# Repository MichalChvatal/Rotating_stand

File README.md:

# Rotating stand controlled by ATtiny Microcontroller (Attiny13)

This repository contains firmware for controlling a 28byj-48 stepper motor using an ATtiny microcontroller. The project is designed to be power-efficient by utilizing the microcontroller's low-power sleep modes and disabling unused peripherals.

The code is written in C and is intended to be compiled with a toolchain for AVR microcontrollers, such as `avr-gcc`.

## Features

* **Selectable Drive Modes:** Choose between three different control modes at compile time:
    * **Single-Phase (Wave Drive):** Optimized for low power consumption (~148 mA).
    * **Dual-Phase (Full Drive):** Provides higher torque at the cost of increased power consumption (~260 mA).
    * **Half-Step:** Offers smoother motion but has higher power consumption (~200 mA).
* **Low Power Consumption:** The firmware is optimized for low power, with the ATtiny microcontroller consuming only 2.3 mA.
* **Timer-Based Control:** The motor is driven by a Timer/Counter0 interrupt, ensuring precise and reliable stepping.
* **Sleep Mode:** The microcontroller enters an Idle sleep mode between steps to further reduce power consumption.

## Hardware Requirements

* **Microcontroller:** ATtiny (The code is based on an ATtiny, but should be adaptable to other AVR microcontrollers).
* **Stepper Motor:** 28byj-48 (5V)
* **Motor Driver:** ULN2003
* **Clock Source:** The microcontroller is configured to use an internal clock of 4.8 MHz.

### PCB Design Files

The repository includes the PCB design files in the `HW` folder. These files can be used to manufacture the custom circuit board for this project.

***

## Configuration

### Fuses

The ATtiny microcontroller's fuses must be configured as follows to achieve the desired clock speed and low power operation:

* **Low Fuse Byte:** `0x79`
* **High Fuse Byte Byte:** `0xFF`

These settings will:
* Set the internal clock to 4.8 MHz.
* Disable the internal clock division by 8.
* Disable the Brown-out Detection (BODLEVEL).
* Disable the Watchdog Timer.

### Drive Mode Selection

You can select the desired drive mode by modifying the `#define` statements at the top of the `main.c` file. Only one mode should be set to `1` at a time.

```c
// Select control type
#define SINGLE_PHASE_CONTROL (1) // Wave drive - Full step; single-phase control. (Consumption 148 mA)
#define DUAL_PHASE_CONTROL   (0) // Full drive - Full step, but higher consumption because I'm powering 2 coils, and higher force; dual-phase control. (Consumption approx. 260 mA)
#define HALF_STEP            (0) // Half step drive - Half step, higher consumption because I'm powering 2 coils. (Consumption approx. 200 mA)

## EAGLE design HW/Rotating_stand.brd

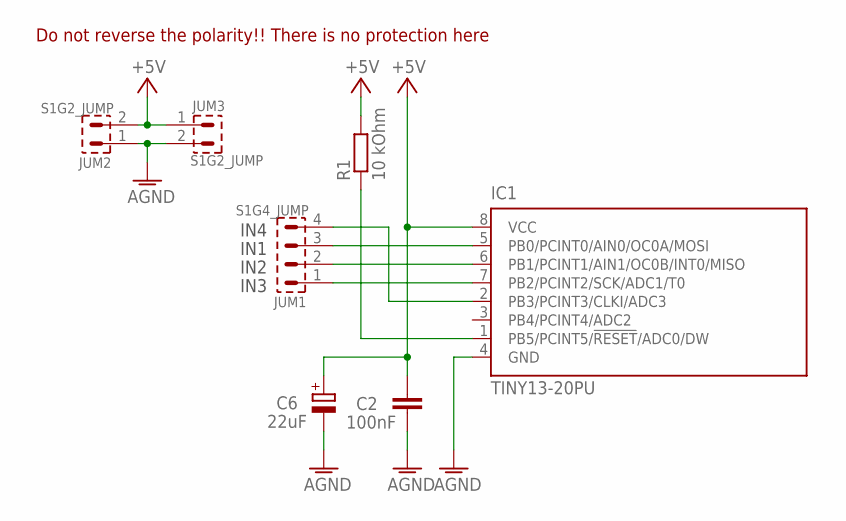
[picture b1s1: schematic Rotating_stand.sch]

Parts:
C2: 100nF; C050-024X044
C6: 22uF; E2,5-5
IC1: TINY13-20PU; DIL08
JUM1: S1G4_JUMP; S1G4_JUM
JUM2, JUM3: S1G2_JUMP; S1G2_JUM
R1: 10 kOhm; 0207/7

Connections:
+5V: C2.1, C6.+, IC1.8 (VCC), JUM2.2, JUM3.1, R1.2
AGND: C2.2, C6.-, IC1.4 (GND), JUM2.1, JUM3.2
unnamed: IC1.1 (PB5/PCINT5/!RESET!/ADC0/DW), R1.1
unnamed: IC1.2 (PB3/PCINT3/CLKI/ADC3), JUM1.4
unnamed: IC1.5 (PB0/PCINT0/AIN0/OC0A/MOSI), JUM1.3
unnamed: IC1.6 (PB1/PCINT1/AIN1/OC0B/INT0/MISO), JUM1.2
unnamed: IC1.7 (PB2/PCINT2/SCK/ADC1/T0), JUM1.1

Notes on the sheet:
Do not reverse the polarity!! There is no protection here
IN1
IN2
IN3
IN4

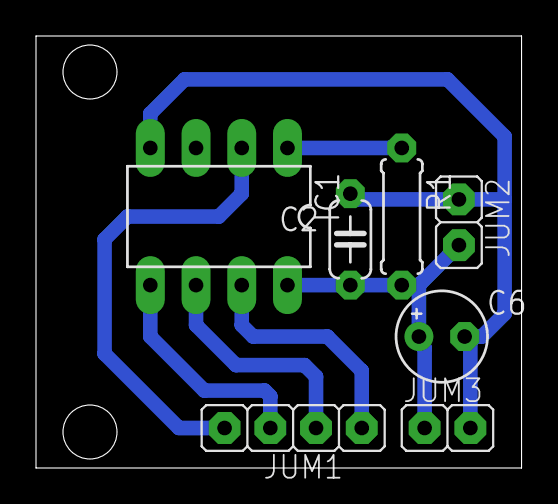
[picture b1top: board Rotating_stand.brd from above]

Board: 2 copper layers, 27.0 x 24.0 mm, 7 parts (0 on the bottom side), 7 nets.

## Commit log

2025-08-22 version 1.0

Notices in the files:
parts and their libraries:
Copyright (C) PaJa 2011-2014
